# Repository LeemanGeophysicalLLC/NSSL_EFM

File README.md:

# Balloon Borne Electric Field Meter

This repository contains all files and relevant information for the electric field meter
(EFM) designed for NSSL. This instrument has been in existance for many years, but beginning
in approximatley 2019/2020 Leeman Geophysical was contracted to help design and implement the
next generation of the device. This README should be a living document keeping the most
current and relevant information on the assembly, operation, and programming of the
instrument.

Where there are other system components that are not directly part of the instrument (such as
the cutdown system), we will link to the relevant documentation.

## Mechanical Parts

A current version of the Fusion 360 project is [here](Mechanical/EFM%20v92.f3z), but be
careful as it is quite a bear with lots of older artifacts from previous revisions and
the assembly isn't completed as that just wasn't necessary to machine the parts.
Please update any changes made!

### Fiberglass Body and Spheres
These are provided by NSSL and we believed to be made by the OU Physics machine shop at some
time in the past. When more are needed we can evaluate the design and manufacturing options
at that time.

### Foams
The electronics for the EFM are protected from the environment (water, wind, and cold) by the
foam paddles that also serve to direct airflow to make the instrument rotate about the Earth
perpendicular axis. The foams are machined from 1" thick blue insulation foam such as
[item 14615](https://www.lowes.com/pd/Dow-Common-1-in-x-4-ft-x-8-ft-Actual-1-in-x-4-ft-x-8-ft-SCOREBOARD-1-R-5-Faced-Polystyrene-Garage-Door-Foam-Board-Insulation-with-Sound-Barrier/1000171587) from Lowe's. We machine these on a
large format router and find that screwing the foam down to the base with drywall screws and
using a downcutting bit result in the best cuts. The foams are still difficult to machine well
as they still try to slide around, pull up, and generate massive amounts of static which can
sometimes cause false trips of the router's limit switch system.

Each end of the instrument has four foam plates. The solid models for the control end foams are
[here](Mechanical/Control_Foam/). The solid models for the motor end foams are
[here](Mechanical/Motor_Foam/).

### Machined Parts
We have tried to keep the number of custom machined parts to a minimum to make field repairs
as easy as possible, but there are a few necessary parts. Namely the "hub" which inserts into
the fiberglass tube body and provides driving force and a place for the fiber optic cable to
exit the tube. This hub is made from 6061 Aluminium and has as much material as possible
removed to make it light. This is very similar to the original design from the machine shop,
but with a much simplified bearing setup. A 2D drawing of the hub is available
[here](Mechanical/Machined_Parts/Hub%20Drawing.pdf).

An aluminium shaft screws into the hubs and passes through bearings to provide a low friction
suspension for the tube. The hub shaft 2D drawing is
[here](Mechanical/Machined_Parts/Hub%20Shaft%20Drawing.pdf). This should be secured into the
hubs with Loctite 242 blue thread locker. The other end has M8 washers (like McMaster
[98689A116](https://www.mcmaster.com/98689A116/)) and nuts (like McMaster
[90592A022](https://www.mcmaster.com/90592A022/)). Use Locktite 272 on the nuts.

The motor driver is a socket-like device that turns the rotating assembly by driving the
nut on the end of the hub shaft. It is secured to the motor shaft with #4 set screws such
as McMaster [98637A105](https://www.mcmaster.com/98637A105/). Use Locktite 272 on the set
screws. A drawing of the part is [here](Mechanical/Machined_Parts/Motor%20Driver%20Drawing.pdf).

### End Caps and Bearings
The end caps that support the rotating load are 3D printed for weight, cost, and simplicity.
The original sets were printed in PLA, but those have proven to be somewhat brittle and NSSL
is testing alternatives. The STL file to print the caps is
[here](Mechanical/3D_Prints/endcap.stl). Be sure to print with supports so that the bearing
pockets on the bottom accept the bearing nicely!

We chose easy to find skateboard bearings (8x22x7 size) such as [these](https://amzn.to/3GVvaEM)
and press them in gently with a socket on the outer bearing race and small hammer. There are
two bearings per endcap. End caps are bolted through the foam to either the fiber optic or
motor plates with nylon hardware #6 size.

* Screws McMaster [95868A312](https://www.mcmaster.com/catalog/128/3430/)
* Washers McMaster [90295A380](https://www.mcmaster.com/catalog/128/3546)
* Nuts McMaster [94812A300](https://www.mcmaster.com/catalog/128/3502/)

### Fiber Optic Plate
The [fiber optic coupler (PN 51 0241)](https://i-fiberoptics.com/connector-detail-mating.php?id=825&cat=mating) is inserted through this plate (use the threaded side and included nut).
The coupler is then cutoff flush with the nut, clearnace drilled, and chambered to allow the
fiberoptic cable to slip and turn in the coupler, but still be aligned with the pigtail
running to the control PCBA.

### Motor Mount Plate
The [motor](https://www.digikey.com/en/products/detail/dfrobot/FIT0441/6588579) mounts
to this simple 3D printed plate and is held onto the foam. The motor mounts
with M3 screws that are 5mm long, such as McMaster
[92000A114](https://www.mcmaster.com/92000a114/). The STL file is
[here](Mechanical/3D_Prints/motor_mount_plate.stl).

### Fiber Optic Cable
We use the plastic cable from Industrial Fiberoptics, part [GH4001](https://www.digikey.com/en/products/detail/industrial-fiber-optics/GH4001/1855657) or similar.

## Circuit Boards
### Analog PCBA

The analog PCBA is really the heart of the EFM and what everything else is in service of. It is
a simple charge amplifier and filter. This design is basically a direct copy of the old EFM
as the charge amplifeir and filter were working just fine. We did some pretty extensive
comparisons between the old and new charge amps as well as testing for any temperature
dependence of the amplifier and filter. 

* [KiCAD Project](PCBs/Analog_PCB/KiCAD_Project)
* [PDF schematic](PCBs/Analog_PCB/PDFs/schematic.pdf)
* [Mechancial Drawing](PCBs/Analog_PCB/PDFs/pcb.pdf)

### Control PCBA

The control PCBA manages the GPS, data logging, and transmitter. This board is easily the most
complex and expensive of the entire unit. There are three processors on the board. While this
is gross overkill, it allows us to easily modify the behavior, move workload, and change
functionality with three relatively simple bits of firmware instead of one more complex bit
that deals with a scheduler. The three functions are receiving fiber/GPS data, writing to the
SD card, and transmitting data. We do plan on moving transmit off the board to its own board
in the future so we can more easily change transmitters. We also need a transmitter evaluation
from NSSL to decide if we stay with XBee, go back to the 433MHz system, or do something
entirely different.

There are indicator lights for the status of the board along the edge
* SD ACT (green) - indicates write activity to the SD Card
* SD Err (red) - blinks at boot, then indicates problems with the SD card system
* XB ACT (green) - indicates write activity to the SD Card
* XB Err (red) - blinks at boot, then indicates problems with the XBee system. It also indicates
when the radio is locked out at startup waiting for the GPS to lock (it is on a timer)
* M ACT (green) - blinks with received data over the fiberoptic link
* GPS (green) - toggles on/off with the receiption of NMEA packets
* PWR (green) - On when battery power is applied

Note, we do not enable the transmitter for some time after boot to allow the GPS to get a lock.
We observed the XBee being active before the GPS locks can greatly increase lock times or in
a few cases even prevent lock.

The two sets of pins with * by the on J4 should be jumpered for the XBee radio to transmit.
You can un-jumper and connect a USB to 3.3V logic cable here to program the XBee radio.

* [KiCAD Project](PCBs/Control_PCB/KiCAD_Project)
* [PDF schematic](PCBs/Control_PCB/PDFs/schematic.pdf)
* [Mechancial Drawing](PCBs/Control_PCB/PDFs/pcb.pdf)

### CR123 Battery PCBA

This PCB is used for power of most items in the EFM for convenience. We tried CR2 batteries
and there is a CR2 board in the repository history, but they didn't have the capacity for all
applications and we didn't want to have yet another battery type on-board. There isn't much
to this board.

* [KiCAD Project](PCBs/CR123_Battery_PCB/KiCAD_Project)
* [PDF schematic](PCBs/CR123_Battery_PCB/PDFs/schematic.pdf)
* [Mechancial Drawing](PCBs/CR123_Battery_PCB/PDFs/pcb.pdf)

### Digital PCBA

The digital PCBA provides power to the analog PCBA, digitizes the charge amplifier, collects
IMU data, temperature, pressure, humidity, and sends it all down the fiber to the control
PCBA in the end foam. This PCB is relatively complex and has multiple IMU footprints as
the supply chain in 2022 has made it difficult to get any IMU, much less the same one over
and over. There is also a delay turn on circuit to help debounce the switch, but it was not
populated in the November 2022 batch as the parts were not available. Performance did not
appear to be impacted. There is an LED (D2) that mirrors the fiber sender for easy visual
confirmatino that data are being sent.

* [KiCAD Project](PCBs/Digital_PCB/KiCAD_Project)
* [PDF schematic](PCBs/Digital_PCB/PDFs/schematic.pdf)
* [Mechancial Drawing](PCBs/Digital_PCB/PDFs/pcb.pdf)

### Motor Control PCBA

The motor control PCBA controls the PWM speed signal to the motor, which is a [DFRobot
FIT0441](https://www.digikey.com/en/products/detail/dfrobot/FIT0441/6588579), by reading
the motor's built in encoder. We target 120 RPM for the motor speed. In the November 2022
run we had to modify the PID coefficients with the newest motors and NSSL reports a slower
rotation rate, making meaning they changed the encoders in the motors. This requires further
investigation.

This board also houses a tone system which can be turned on to play a series of tones after
the motor has been detected as stalled. The motor cutoff on stall can be enabled or disabled.
At NSSL's request, if enabled, the motor will attempt to restart after approximately 1 minute.

* [KiCAD Project](PCBs/Motor_Control_PCB/KiCAD_Project)
* [PDF schematic](PCBs/Motor_Control_PCB/PDFs/schematic.pdf)
* [Mechancial Drawing](PCBs/Motor_Control_PCB/PDFs/pcb.pdf)

### Tracker PCBA

The tracker is designed to radio a GPS position and altitude to the Rock7 satellite network
to help with getting the instrument back. It also passes cutdown messages to the cutdown
module from satellite via a short-range XBee link.

* [KiCAD Project](PCBs/Tracker_PCB/KiCAD_Project)
* [PDF schematic](PCBs/Tracker_PCB/PDFs/schematic.pdf)
* [Mechancial Drawing](PCBs/Tracker_PCB/PDFs/pcb.pdf)

# Design Decisions Captured
* NSSL requested the tracker be independent from the rest of the instrument to allow it to be
used on other instruments and as a fully independent system.
* NSSL requested the cutdown be entire sepearte and as low cost as possible as these are not
always retreived. Hence the decision to NOT put a sat modem on it and/or combine it with the
tracker. There were also concerns of the train becoming seperated and not having a tracker
directly embedded with the expensive EFM or other instrument.

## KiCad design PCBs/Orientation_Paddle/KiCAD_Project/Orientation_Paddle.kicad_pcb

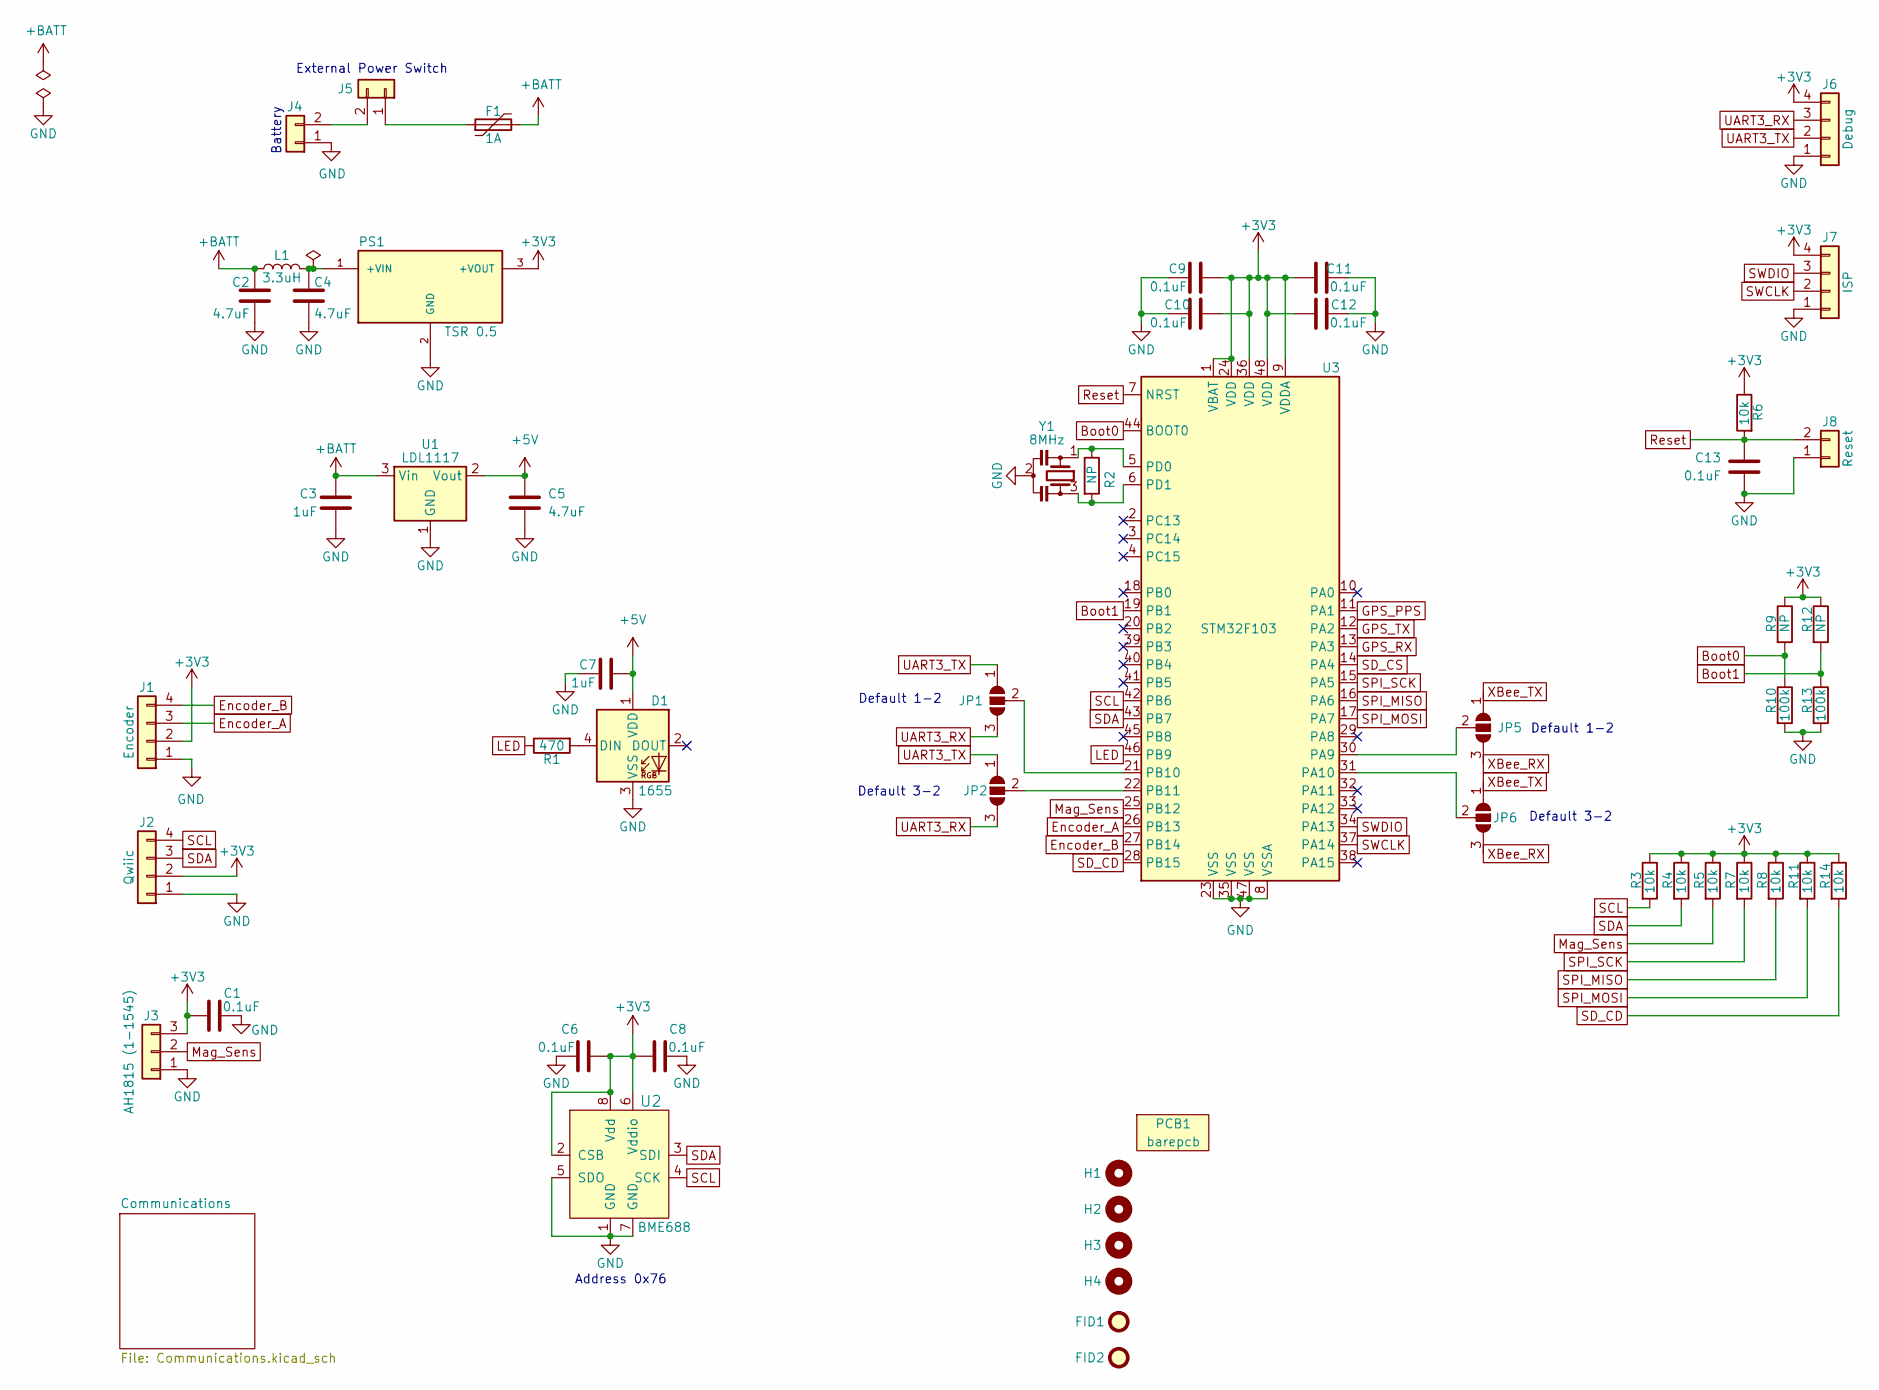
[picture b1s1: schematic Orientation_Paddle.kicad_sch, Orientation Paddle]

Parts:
C1, C6, C8, C9, C10, C11, C12, C13: 1-0000007
C2, C4: 1-0000136
C3, C7: 1-0000018
C5: 1-0000019
D1: 1-0000399
F1: 1-0001517
FID1, FID2: Fiducial_1mm_2mm; Fiducial_1mm_Mask2mm
H1, H2, H3, H4: Imperial6; MountingHole_imperial6
J1: NP_Conn_01x04_Relief; SolderWire_1x04_Relief
J2: 1-0001205
J3: NP_Conn_01x03_Relief; SolderWire_1x03_Relief
J4, J5: NP_Conn_01x02_Relief; SolderWire_1x02_Relief
J6, J7: NP_Conn_01x04; PinHeader_1x04_P2.54mm_Vertical
J8: NP_Conn_01x02; PinHeader_1x02_P2.54mm_Vertical
JP1, JP2, JP5, JP6: SolderJumper_3_Open; SolderJumper-3_P1.3mm_Open_RoundedPad1.0x1.5mm_NumberLabels
L1: 1-0000931
PCB1: barepcb
PS1: 1-0000727
R1: 1-0000679
R2: 1-0000009
R3, R4, R5, R6, R7, R8, R11, R14: 1-0000010
R9, R12: 1-0000006
R10, R13: 1-0000174
U1: 1-0001232
U2: 1-0001471
U3: 1-0000207
Y1: 1-0000721

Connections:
+3V3: C1.1, C6.2, C8.1, C9.1, C10.1, C11.1, C12.1, J1.2, J2.2, J3.3, J6.4, J7.4, PS1.3 (+VOUT), R3.1, R4.1, R5.1, R6.1, R7.1, R8.1, R9.1, R11.1, R12.1, R14.1, U2.2 (CSB), U2.6 (Vddio), U2.8 (Vdd), U3.1 (VBAT), U3.9 (VDDA), U3.24 (VDD), U3.36 (VDD), U3.48 (VDD); also elsewhere on the board
+5V: C5.1, C7.1, D1.1 (VDD), U1.2 (Vout)
+BATT: C2.1, C3.1, F1.2, L1.1, U1.3 (Vin)
Boot0: R9.2, R10.1, U3.44 (BOOT0)
Boot1: R12.2, R13.1, U3.19 (PB1)
Encoder_A: J1.3, U3.26 (PB13)
Encoder_B: J1.4, U3.27 (PB14)
GND: C1.2, C2.2, C3.2, C4.2, C5.2, C6.1, C7.2, C8.2, C9.2, C10.2, C11.2, C12.2, C13.2, D1.3 (VSS), J1.1, J2.1, J3.1, J4.1, J6.1, J7.1, J8.1, PS1.2 (GND), R10.2, R13.2, U1.1 (GND), U2.1 (GND), U2.5 (SDO), U2.7 (GND), U3.8 (VSSA), U3.23 (VSS), U3.35 (VSS), U3.47 (VSS), Y1.2; also elsewhere on the board
GPS_PPS: U3.11 (PA1); also elsewhere on the board
GPS_RX: U3.13 (PA3); also elsewhere on the board
GPS_TX: U3.12 (PA2); also elsewhere on the board
LED: R1.1, U3.46 (PB9)
Mag_Sens: J3.2, R5.2, U3.25 (PB12)
unnamed: D1.4 (DIN), R1.2
unnamed: J4.2, J5.2
unnamed: F1.1, J5.1
unnamed: JP1.2 (C), U3.21 (PB10)
unnamed: JP2.2 (C), U3.22 (PB11)
unnamed: JP5.2 (C), U3.30 (PA9)
unnamed: JP6.2 (C), U3.31 (PA10)
unnamed: C4.1, L1.2, PS1.1 (+VIN)
unnamed: R2.1, U3.5 (PD0), Y1.1
unnamed: R2.2, U3.6 (PD1), Y1.3
Reset: C13.1, J8.2, R6.2, U3.7 (NRST); also elsewhere on the board
SCL: J2.4, R3.2, U2.4 (SCK), U3.42 (PB6)
SDA: J2.3, R4.2, U2.3 (SDI), U3.43 (PB7)
SD_CD: R14.2, U3.28 (PB15); also elsewhere on the board
SD_CS: U3.14 (PA4); also elsewhere on the board
SPI_MISO: R8.2, U3.16 (PA6); also elsewhere on the board
SPI_MOSI: R11.2, U3.17 (PA7); also elsewhere on the board
SPI_SCK: R7.2, U3.15 (PA5); also elsewhere on the board
SWCLK: J7.2, U3.37 (PA14)
SWDIO: J7.3, U3.34 (PA13)
UART3_RX: J6.3, JP1.3 (B), JP2.3 (B)
UART3_TX: J6.2, JP1.1 (A), JP2.1 (A)
XBee_RX: JP5.3 (B), JP6.3 (B); also elsewhere on the board
XBee_TX: JP5.1 (A), JP6.1 (A); also elsewhere on the board

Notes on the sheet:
Default 1-2
Battery
Address 0x76
External Power Switch
Default 3-2

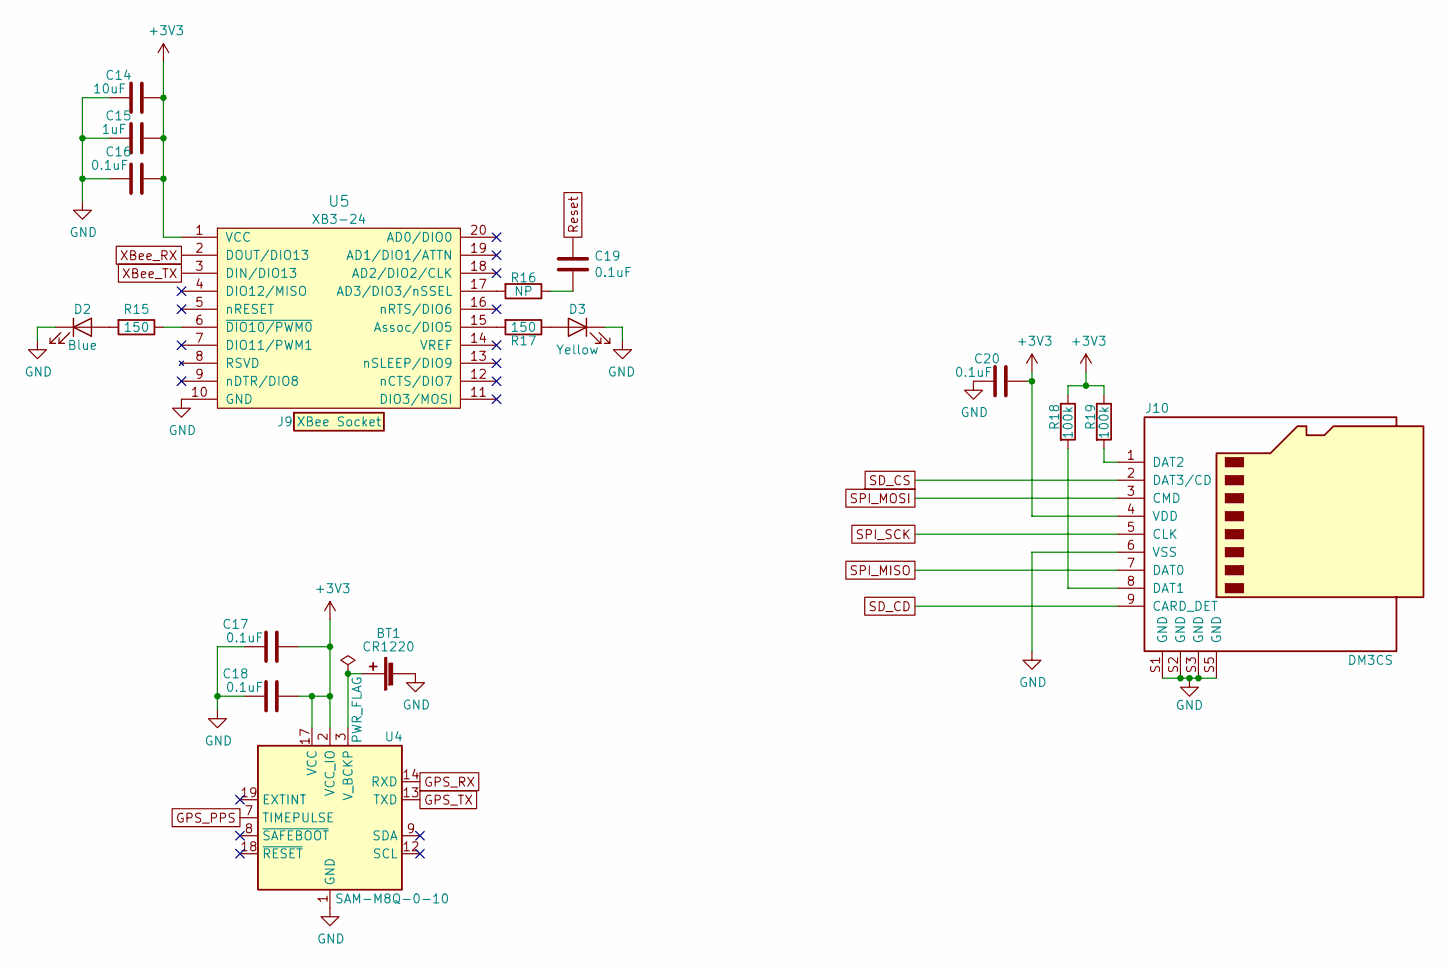
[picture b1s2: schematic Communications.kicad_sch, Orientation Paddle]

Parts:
BT1: 1-0000246
C14: 1-0000075
C15: 1-0000018
C16, C17, C18, C19, C20: 1-0000007
D2: 1-0000599
D3: 1-0000601
J9: 1-0000050
J10: 1-0000190
R15, R17: 1-0000008
R16: 1-0000006
R18, R19: 1-0000174
U4: 1-0000446
U5: 1-0000785

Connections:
+3V3: C14.1, C15.1, C16.1, C17.1, C18.1, C20.2, J10.4 (VDD), R18.1, R19.1, U4.2 (VCC_IO), U4.17 (VCC), U5.1 (VCC); also elsewhere on the board
GND: BT1.2 (-), C14.2, C15.2, C16.2, C17.2, C18.2, C20.1, D2.1 (K), D3.1 (K), J10.6 (VSS), J10.S1 (GND), J10.S2 (GND), J10.S3 (GND), J10.S5 (GND), U4.1 (GND), U4.4 (GND), U4.5 (GND), U4.6 (GND), U4.10 (GND), U4.11 (GND), U4.15 (GND), U4.16 (GND), U4.20 (GND), U5.10 (GND); also elsewhere on the board
GPS_PPS: U4.7 (TIMEPULSE); also elsewhere on the board
GPS_RX: U4.14 (RXD); also elsewhere on the board
GPS_TX: U4.13 (TXD); also elsewhere on the board
unnamed: BT1.1 (+), U4.3 (V_BCKP)
unnamed: C19.2, R16.1
unnamed: D2.2 (A), R15.2
unnamed: D3.2 (A), R17.1
unnamed: J10.8 (DAT1), R18.2
unnamed: J10.1 (DAT2), R19.2
unnamed: R16.2, U5.17 (AD3/DIO3/nSSEL)
unnamed: R17.2, U5.15 (Assoc/DIO5)
unnamed: R15.1, U5.6 (~DIO10/PWM0)
Reset: C19.1; also elsewhere on the board
SD_CD: J10.9 (CARD_DET); also elsewhere on the board
SD_CS: J10.2 (DAT3/CD); also elsewhere on the board
SPI_MISO: J10.7 (DAT0); also elsewhere on the board
SPI_MOSI: J10.3 (CMD); also elsewhere on the board
SPI_SCK: J10.5 (CLK); also elsewhere on the board
XBee_RX: U5.2 (DOUT/DIO13); also elsewhere on the board
XBee_TX: U5.3 (DIN/DIO13); also elsewhere on the board

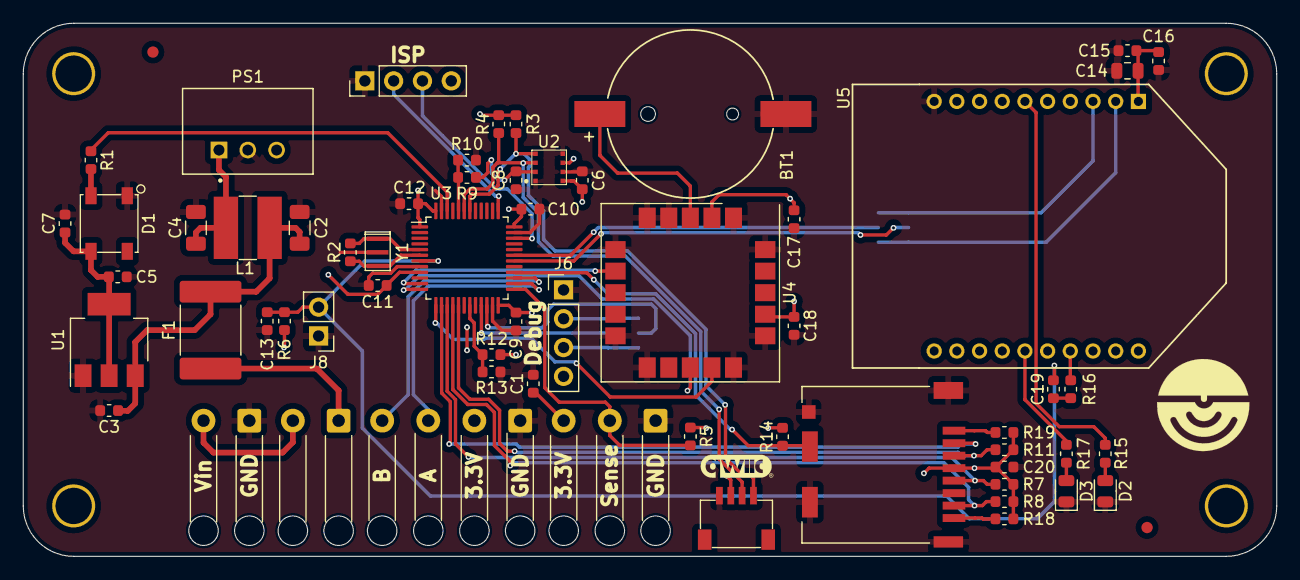
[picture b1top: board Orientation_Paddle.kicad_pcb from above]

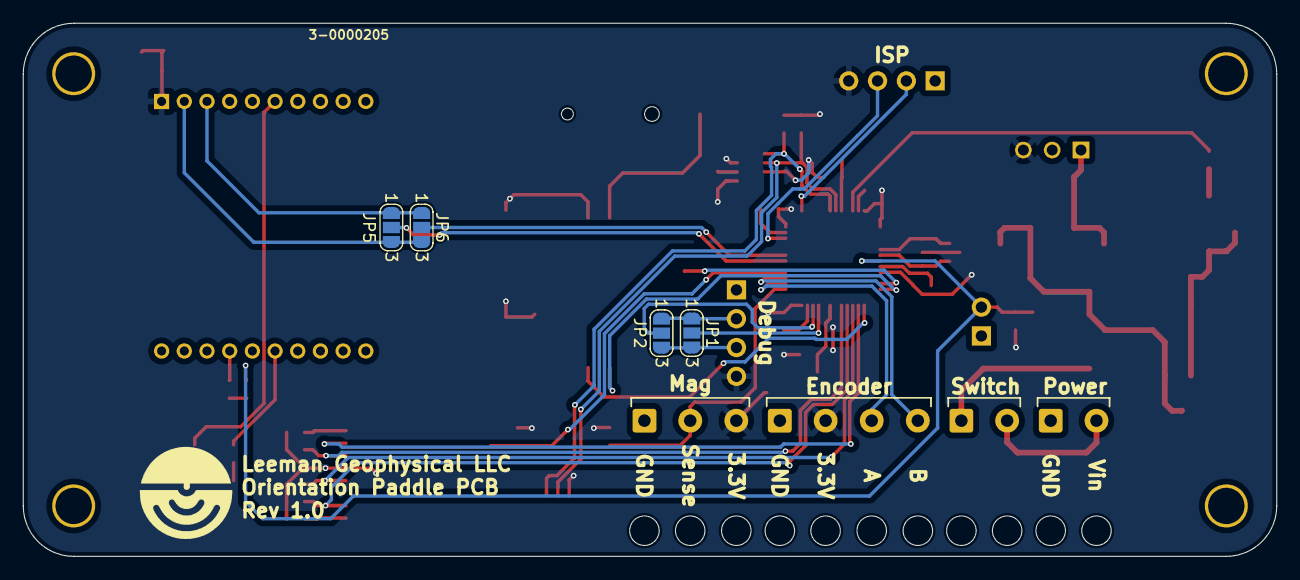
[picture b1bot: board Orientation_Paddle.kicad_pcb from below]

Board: 2 copper layers, 110.5 x 47.0 mm, 73 parts (4 on the bottom side), 46 nets.

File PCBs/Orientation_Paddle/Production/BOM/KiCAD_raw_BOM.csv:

"Reference","Value","Datasheet","Footprint","Qty","Internal Part Number","PValue","Populated"
"BT1","1-0000246","","batteries:1-0000246","1","1-0000246","CR1220","1"
"C1","1-0000007","~","capacitors_0603:1-0000007","1","1-0000007","0.1uF","1"
"C2","1-0000136","~","capacitors_1206:1-0000136","1","1-0000136","4.7uF","1"
"C3","1-0000018","~","capacitors_0603:1-0000018","1","1-0000018","1uF","1"
"C4","1-0000136","~","capacitors_1206:1-0000136","1","1-0000136","4.7uF","1"
"C5","1-0000019","~","capacitors_0603:1-0000019","1","1-0000019","4.7uF","1"
"C6","1-0000007","~","capacitors_0603:1-0000007","1","1-0000007","0.1uF","1"
"C7","1-0000018","~","capacitors_0603:1-0000018","1","1-0000018","1uF","1"
"C8","1-0000007","~","capacitors_0603:1-0000007","1","1-0000007","0.1uF","1"
"C9","1-0000007","~","capacitors_0603:1-0000007","1","1-0000007","0.1uF","1"
"C10","1-0000007","~","capacitors_0603:1-0000007","1","1-0000007","0.1uF","1"
"C11","1-0000007","~","capacitors_0603:1-0000007","1","1-0000007","0.1uF","1"
"C12","1-0000007","~","capacitors_0603:1-0000007","1","1-0000007","0.1uF","1"
"C13","1-0000007","~","capacitors_0603:1-0000007","1","1-0000007","0.1uF","1"
"C14","1-0000075","~","capacitors_0805:1-0000075","1","1-0000075","10uF","1"
"C15","1-0000018","~","capacitors_0603:1-0000018","1","1-0000018","1uF","1"
"C16","1-0000007","~","capacitors_0603:1-0000007","1","1-0000007","0.1uF","1"
"C17","1-0000007","~","capacitors_0603:1-0000007","1","1-0000007","0.1uF","1"
"C18","1-0000007","~","capacitors_0603:1-0000007","1","1-0000007","0.1uF","1"
"C19","1-0000007","~","capacitors_0603:1-0000007","1","1-0000007","0.1uF","0"
"C20","1-0000007","~","capacitors_0603:1-0000007","1","1-0000007","0.1uF","1"
"D1","1-0000399","","leds_other:1-0000399","1","1-0000399","1655","1"
"D2","1-0000599","~","leds_0805:1-0000599","1","1-0000599","Blue","1"
"D3","1-0000601","~","leds_0805:1-0000601","1","1-0000601","Yellow","1"
"F1","1-0001517","~","fuses:1-0001517","1","1-0001517","1A","1"
"FID1","Fiducial_1mm_2mm","~","mechanical:Fiducial_1mm_Mask2mm","1","0-0000000","Fiducial","0"
"FID2","Fiducial_1mm_2mm","~","mechanical:Fiducial_1mm_Mask2mm","1","0-0000000","Fiducial","0"
"H1","Imperial6","None","mechanical:MountingHole_imperial6","1","0-0000000","M3","0"
"H2","Imperial6","None","mechanical:MountingHole_imperial6","1","0-0000000","M3","0"
"H3","Imperial6","None","mechanical:MountingHole_imperial6","1","0-0000000","M3","0"
"H4","Imperial6","None","mechanical:MountingHole_imperial6","1","0-0000000","M3","0"
"J1","NP_Conn_01x04_Relief","~","np_connectors:SolderWire_1x04_Relief","1","0-0000000","Encoder","0"
"J2","1-0001205","~","connectors:1-0001205","1","1-0001205","Qwiic","1"
"J3","NP_Conn_01x03_Relief","~","np_connectors:SolderWire_1x03_Relief","1","0-0000000","AH1815 (1-1545)","0"
"J4","NP_Conn_01x02_Relief","~","np_connectors:SolderWire_1x02_Relief","1","0-0000000","NP_Conn_01x02","0"
"J5","NP_Conn_01x02_Relief","~","np_connectors:SolderWire_1x02_Relief","1","0-0000000","NP_Conn_01x02","0"
"J6","NP_Conn_01x04","~","np_connectors:PinHeader_1x04_P2.54mm_Vertical","1","0-0000000","Debug","0"
"J7","NP_Conn_01x04","~","np_connectors:PinHeader_1x04_P2.54mm_Vertical","1","0-0000000","ISP","0"
"J8","NP_Conn_01x02","~","np_connectors:PinHeader_1x02_P2.54mm_Vertical","1","0-0000000","Reset","0"
"J9","1-0000050","~","connectors:1-0000050","1","1-0000050","XBee Socket","1"
"J10","1-0000190","","connectors:1-0000190","1","1-0000190","DM3CS","1"
"JP1","SolderJumper_3_Open","~","Jumper:SolderJumper-3_P1.3mm_Open_RoundedPad1.0x1.5mm_NumberLabels","1","","",""
"JP2","SolderJumper_3_Open","~","Jumper:SolderJumper-3_P1.3mm_Open_RoundedPad1.0x1.5mm_NumberLabels","1","","",""
"JP5","SolderJumper_3_Open","~","Jumper:SolderJumper-3_P1.3mm_Open_RoundedPad1.0x1.5mm_NumberLabels","1","","",""
"JP6","SolderJumper_3_Open","~","Jumper:SolderJumper-3_P1.3mm_Open_RoundedPad1.0x1.5mm_NumberLabels","1","","",""
"L1","1-0000931","","inductors:1-0000931","1","1-0000931","3.3uH","1"
"PCB1","barepcb","","misc:barepcb","1","3-0000205","Bare PCB","1"
"PS1","1-0000727","","dc_dc_converters:1-0000727","1","1-0000727","TSR 0.5","1"
"R1","1-0000679","~","resistors_0603:1-0000679","1","1-0000679","470","1"
"R2","1-0000009","~","resistors_0603:1-0000009","1","1-0000009","NP","0"
"R3","1-0000010","~","resistors_0603:1-0000010","1","1-0000010","10k","1"
"R4","1-0000010","~","resistors_0603:1-0000010","1","1-0000010","10k","1"
"R5","1-0000010","~","resistors_0603:1-0000010","1","1-0000010","10k","1"
"R6","1-0000010","~","resistors_0603:1-0000010","1","1-0000010","10k","1"
"R7","1-0000010","~","resistors_0603:1-0000010","1","1-0000010","10k","1"
"R8","1-0000010","~","resistors_0603:1-0000010","1","1-0000010","10k","1"
"R9","1-0000006","~","resistors_0603:1-0000006","1","1-0000006","NP","0"
"R10","1-0000174","~","resistors_0603:1-0000174","1","1-0000174","100k","1"
"R11","1-0000010","~","resistors_0603:1-0000010","1","1-0000010","10k","1"
"R12","1-0000006","~","resistors_0603:1-0000006","1","1-0000006","NP","0"
"R13","1-0000174","~","resistors_0603:1-0000174","1","1-0000174","100k","1"
"R14","1-0000010","~","resistors_0603:1-0000010","1","1-0000010","10k","1"
"R15","1-0000008","~","resistors_0603:1-0000008","1","1-0000008","150","1"
"R16","1-0000006","~","resistors_0603:1-0000006","1","1-0000006","NP","0"
"R17","1-0000008","~","resistors_0603:1-0000008","1","1-0000008","150","1"
"R18","1-0000174","~","resistors_0603:1-0000174","1","1-0000174","100k","1"
"R19","1-0000174","~","resistors_0603:1-0000174","1","1-0000174","100k","1"
"U1","1-0001232","","regulators:1-0001232","1","1-0001232","LDL1117","1"
"U2","1-0001471","","sensors:1-0001471","1","1-0001471","BME688","1"
"U3","1-0000207","","microcontrollers:1-0000207","1","1-0000207","STM32F103","1"
"U4","1-0000446","","others:1-0000446","1","1-0000446","SAM-M8Q-0-10","1"
"U5","1-0000785","","others:1-0000785","1","1-0000785","XB3-24","1"
"Y1","1-0000721","~","crystals_resonators:1-0000721","1","1-0000721","8MHz","1"

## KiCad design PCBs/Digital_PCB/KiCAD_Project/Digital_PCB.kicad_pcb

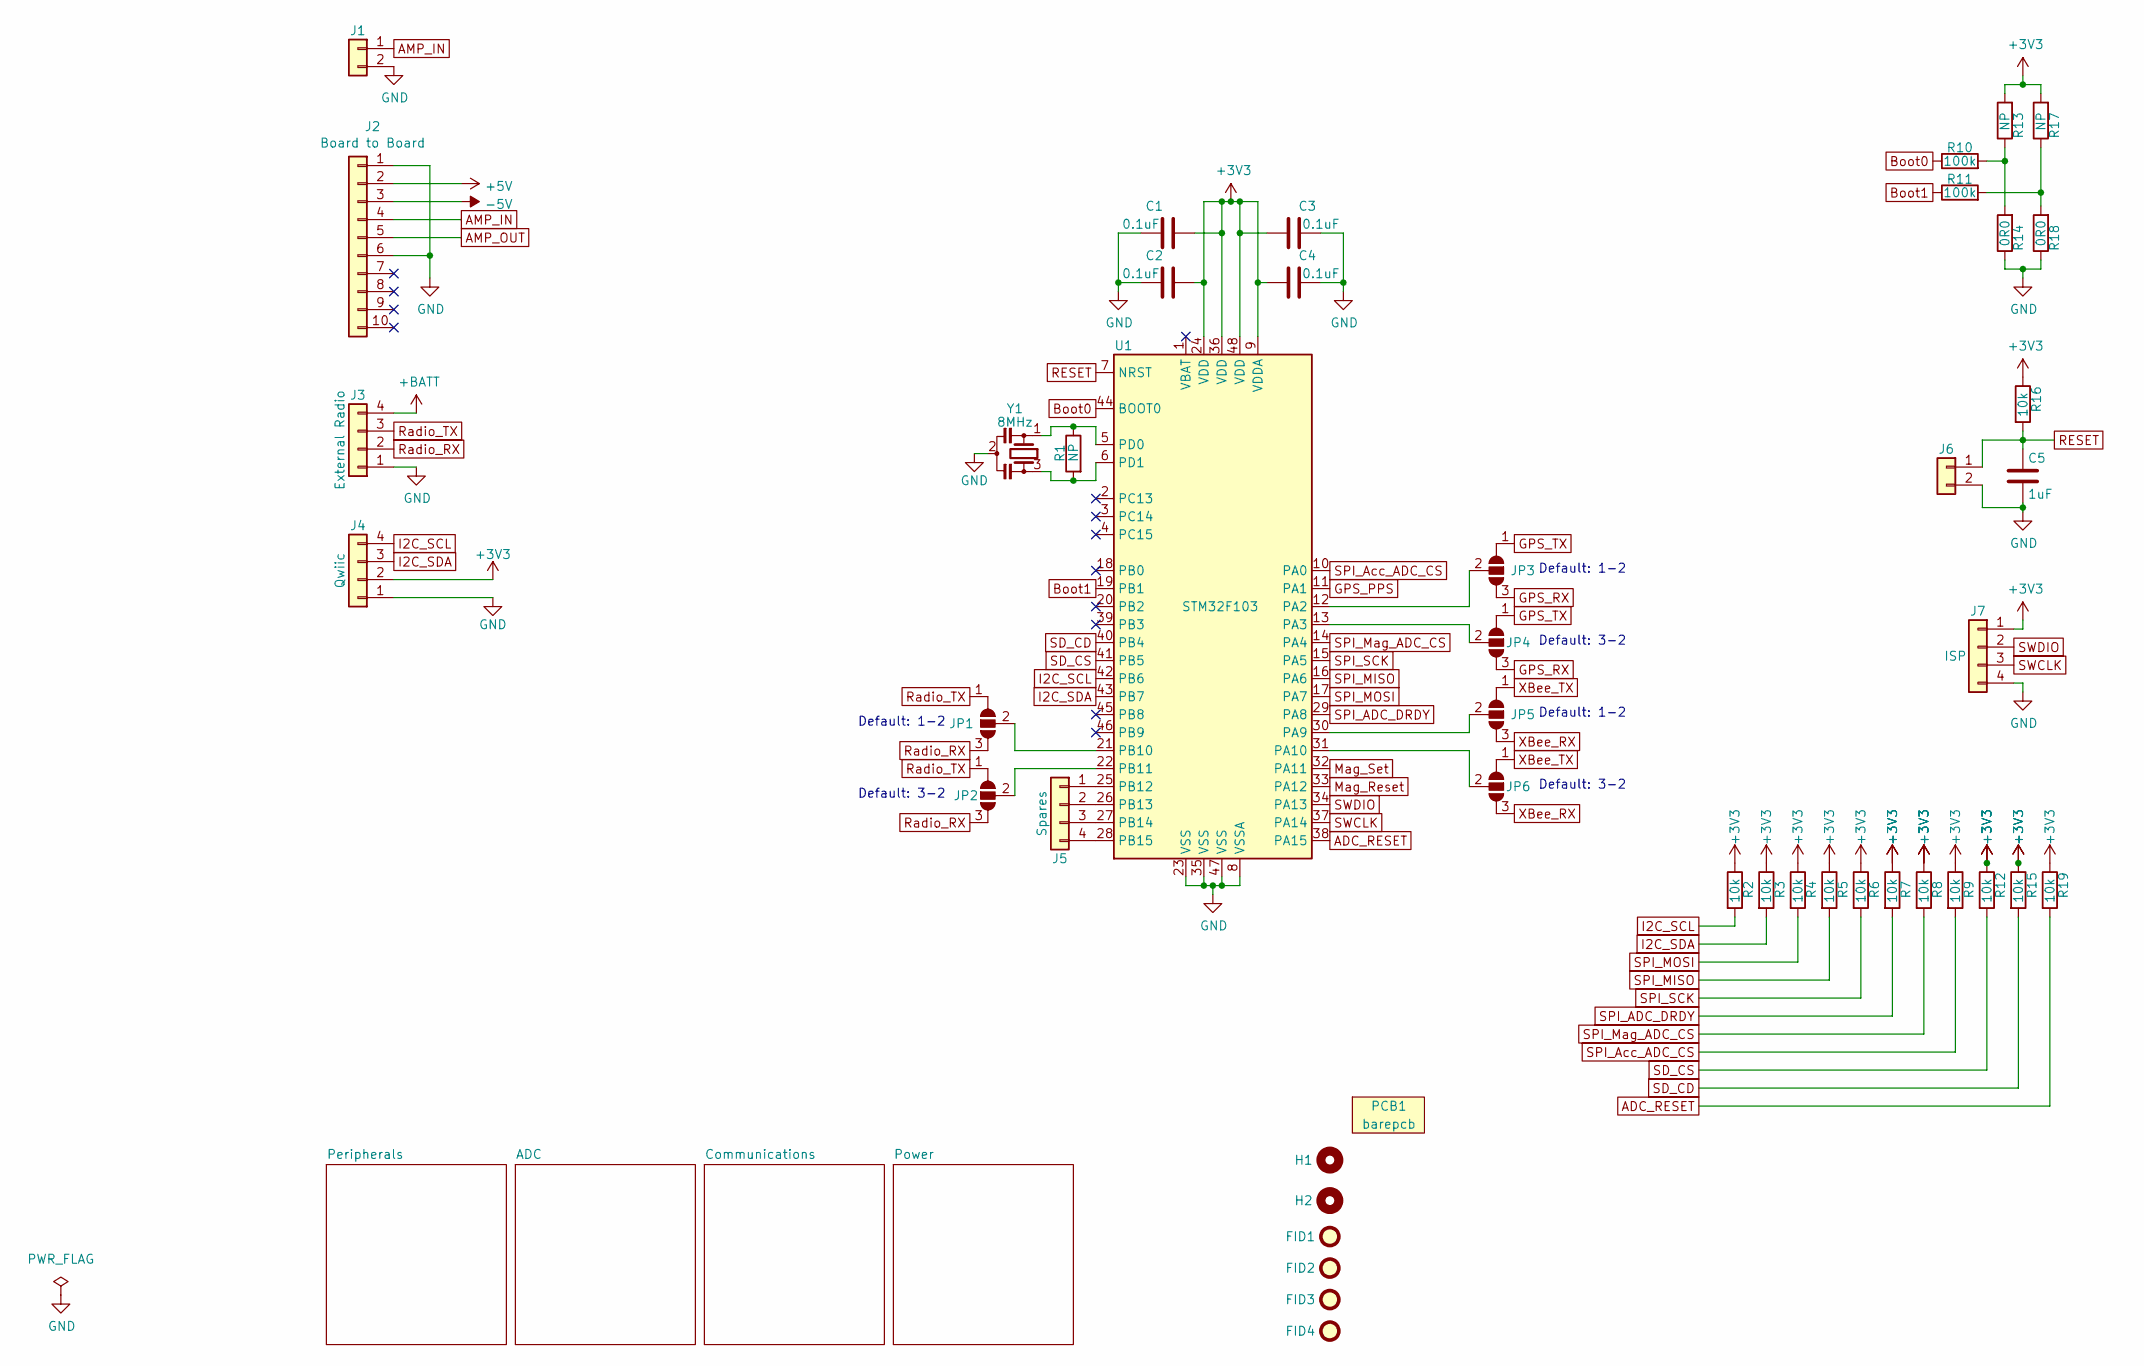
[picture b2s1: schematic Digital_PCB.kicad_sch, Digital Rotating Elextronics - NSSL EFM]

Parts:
C1, C2, C3, C4: 1-0000007
C5: 1-0000018
FID1, FID2, FID3, FID4: Fiducial_1mm_2mm; Fiducial_1mm_Mask2mm
H1, H2: Imperial6; MountingHole_imperial6
J1: NP_Conn_01x02_Relief; SolderWire_1x02_Relief
J2: Board to Board; PinHeader_1x10_P2.54mm_Vertical
J3: NP_Conn_01x04_Relief; SolderWire_1x04_Relief
J4: 1-0001205
J5, J7: NP_Conn_01x04; PinHeader_1x04_P2.54mm_Vertical
J6: NP_Conn_01x02_Relief; PinHeader_1x02_P2.54mm_Vertical
JP1, JP2, JP3, JP4, JP5, JP6: SolderJumper_3_Open; SolderJumper-3_P1.3mm_Open_RoundedPad1.0x1.5mm_NumberLabels
PCB1: barepcb
R1, R13, R14, R17, R18: 1-0000006
R2, R3, R4, R5, R6, R7, R8, R9, R12, R15, R16, R19: 1-0000010
R10, R11: 1-0000174
U1: 1-0000207
Y1: 1-0000721

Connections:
+3V3: C1.2, C2.2, C3.2, C4.2, J4.2, J7.1, R2.1, R3.1, R4.1, R5.1, R6.1, R7.1, R8.1, R9.1, R12.1, R13.2, R15.1, R16.1, R17.2, R19.1, U1.9 (VDDA), U1.24 (VDD), U1.36 (VDD), U1.48 (VDD); also elsewhere on the board
+5V: J2.2; also elsewhere on the board
+BATT: J3.4; also elsewhere on the board
-5V: J2.3; also elsewhere on the board
ADC_RESET: R19.2, U1.38 (PA15); also elsewhere on the board
AMP_IN: J1.1, J2.4
AMP_OUT: J2.5; also elsewhere on the board
Boot0: R10.1, U1.44 (BOOT0)
Boot1: R11.1, U1.19 (PB1)
GND: C1.1, C2.1, C3.1, C4.1, C5.2, J1.2, J2.1, J2.6, J3.1, J4.1, J6.2, J7.4, R14.1, R18.1, U1.8 (VSSA), U1.23 (VSS), U1.35 (VSS), U1.47 (VSS), Y1.2; also elsewhere on the board
GPS_PPS: U1.11 (PA1); also elsewhere on the board
GPS_RX: JP3.3 (B), JP4.3 (B); also elsewhere on the board
GPS_TX: JP3.1 (A), JP4.1 (A); also elsewhere on the board
I2C_SCL: J4.4, R2.2, U1.42 (PB6); also elsewhere on the board
I2C_SDA: J4.3, R3.2, U1.43 (PB7); also elsewhere on the board
Mag_Reset: U1.33 (PA12); also elsewhere on the board
Mag_Set: U1.32 (PA11); also elsewhere on the board
unnamed: J5.1, U1.25 (PB12)
unnamed: J5.2, U1.26 (PB13)
unnamed: J5.3, U1.27 (PB14)
unnamed: J5.4, U1.28 (PB15)
unnamed: JP1.2 (C), U1.21 (PB10)
unnamed: JP2.2 (C), U1.22 (PB11)
unnamed: JP3.2 (C), U1.12 (PA2)
unnamed: JP4.2 (C), U1.13 (PA3)
unnamed: JP5.2 (C), U1.30 (PA9)
unnamed: JP6.2 (C), U1.31 (PA10)
unnamed: R10.2, R13.1, R14.2
unnamed: R11.2, R17.1, R18.2
unnamed: R1.1, U1.5 (PD0), Y1.1
unnamed: R1.2, U1.6 (PD1), Y1.3
RESET: C5.1, J6.1, R16.2, U1.7 (NRST); also elsewhere on the board
Radio_RX: J3.2, JP1.3 (B), JP2.3 (B)
Radio_TX: J3.3, JP1.1 (A), JP2.1 (A)
SD_CD: R15.2, U1.40 (PB4); also elsewhere on the board
SD_CS: R12.2, U1.41 (PB5); also elsewhere on the board
SPI_ADC_DRDY: R7.2, U1.29 (PA8); also elsewhere on the board
SPI_Acc_ADC_CS: R9.2, U1.10 (PA0); also elsewhere on the board
SPI_MISO: R5.2, U1.16 (PA6); also elsewhere on the board
SPI_MOSI: R4.2, U1.17 (PA7); also elsewhere on the board
SPI_Mag_ADC_CS: R8.2, U1.14 (PA4); also elsewhere on the board
SPI_SCK: R6.2, U1.15 (PA5); also elsewhere on the board
SWCLK: J7.3, U1.37 (PA14)
SWDIO: J7.2, U1.34 (PA13)
XBee_RX: JP5.3 (B), JP6.3 (B); also elsewhere on the board
XBee_TX: JP5.1 (A), JP6.1 (A); also elsewhere on the board

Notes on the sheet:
Default: 3-2
Default: 1-2

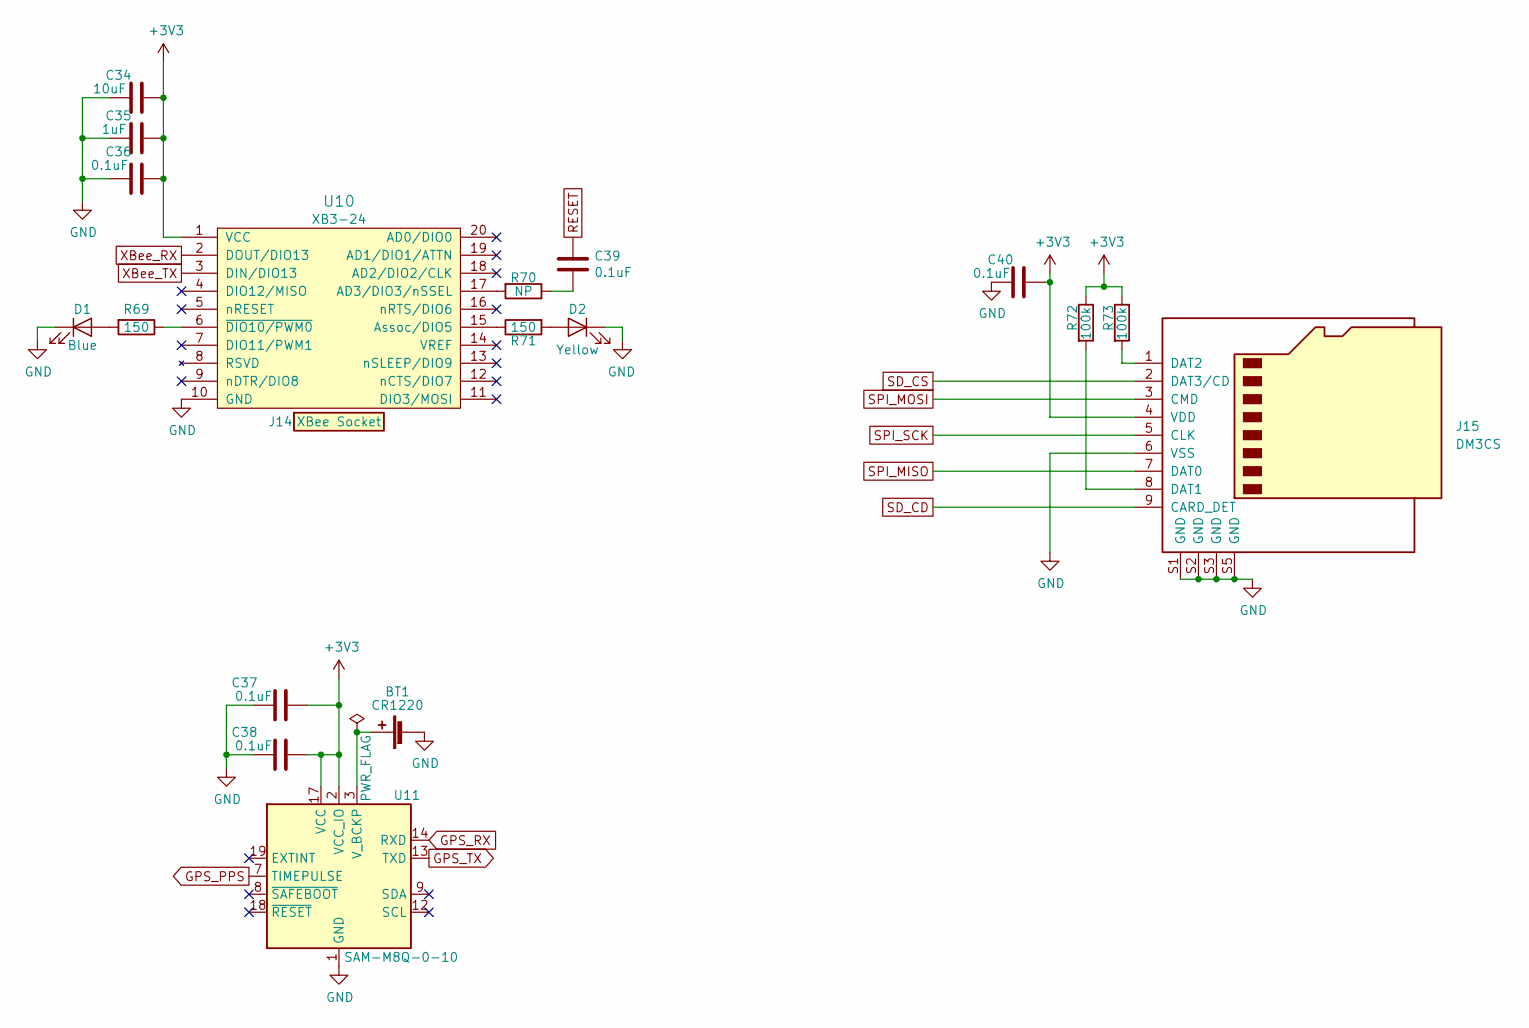
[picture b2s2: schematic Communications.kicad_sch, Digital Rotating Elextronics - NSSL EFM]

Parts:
BT1: 1-0000246
C34: 1-0000075
C35: 1-0000018
C36, C37, C38, C39, C40: 1-0000007
D1: 1-0000599
D2: 1-0000601
J14: 1-0000050
J15: 1-0000190
R69, R71: 1-0000008
R70: 1-0000006
R72, R73: 1-0000174
U10: 1-0000785
U11: 1-0000446

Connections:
+3V3: C34.1, C35.1, C36.1, C37.1, C38.1, C40.2, J15.4 (VDD), R72.1, R73.1, U10.1 (VCC), U11.2 (VCC_IO), U11.17 (VCC); also elsewhere on the board
GND: BT1.2 (-), C34.2, C35.2, C36.2, C37.2, C38.2, C40.1, D1.1 (K), D2.1 (K), J15.6 (VSS), J15.S1 (GND), J15.S2 (GND), J15.S3 (GND), J15.S5 (GND), U10.10 (GND), U11.1 (GND), U11.4 (GND), U11.5 (GND), U11.6 (GND), U11.10 (GND), U11.11 (GND), U11.15 (GND), U11.16 (GND), U11.20 (GND); also elsewhere on the board
GPS_PPS: U11.7 (TIMEPULSE); also elsewhere on the board
GPS_RX: U11.14 (RXD); also elsewhere on the board
GPS_TX: U11.13 (TXD); also elsewhere on the board
unnamed: BT1.1 (+), U11.3 (V_BCKP)
unnamed: C39.2, R70.1
unnamed: D1.2 (A), R69.2
unnamed: D2.2 (A), R71.2
unnamed: J15.8 (DAT1), R72.2
unnamed: J15.1 (DAT2), R73.2
unnamed: R70.2, U10.17 (AD3/DIO3/nSSEL)
unnamed: R71.1, U10.15 (Assoc/DIO5)
unnamed: R69.1, U10.6 (~DIO10/PWM0)
RESET: C39.1; also elsewhere on the board
SD_CD: J15.9 (CARD_DET); also elsewhere on the board
SD_CS: J15.2 (DAT3/CD); also elsewhere on the board
SPI_MISO: J15.7 (DAT0); also elsewhere on the board
SPI_MOSI: J15.3 (CMD); also elsewhere on the board
SPI_SCK: J15.5 (CLK); also elsewhere on the board
XBee_RX: U10.2 (DOUT/DIO13); also elsewhere on the board
XBee_TX: U10.3 (DIN/DIO13); also elsewhere on the board

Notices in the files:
parts and their libraries:
Copyright 2016 Accelerated Designs. All rights reserved.
